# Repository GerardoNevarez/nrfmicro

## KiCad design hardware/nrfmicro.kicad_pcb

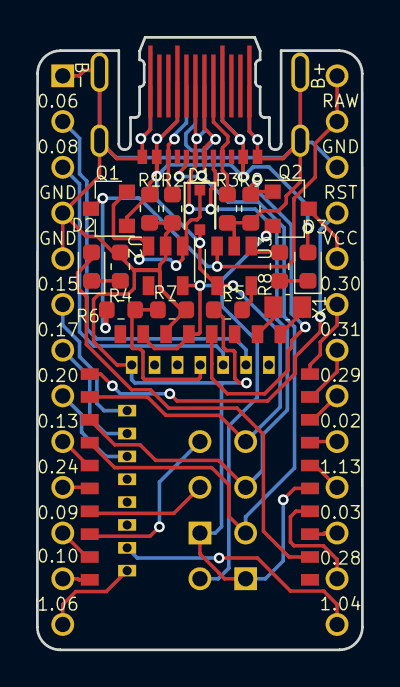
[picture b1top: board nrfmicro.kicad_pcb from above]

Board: 2 copper layers, 18.1 x 34.0 mm, 24 parts (0 on the bottom side), 40 nets.

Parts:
D1: 1N5819; D_SOD-323F
D2: BLUE; LED_0603_1608Metric
D3: RED; LED_0603_1608Metric
J1: USB-C Conn; USB-C_C168688
J2: SWD; connector_swd
J3: Ex_Bat; connector_bat
J4: Ex_USB; connector_usb
J5: USB-C Conn; USB-C-PCB
Q1, Q2: AO3407; SOT-23
R1: 100K; R_0603_1608Metric
R2, R3: 5.1K; R_0603_1608Metric
R4, R8: 1K; R_0603_1608Metric
R5: RPROG; R_0603_1608Metric
R6: 820K; R_0603_1608Metric
R7, R9: 2M; R_0603_1608Metric
U1: E73-2G4M08S1C; E73-2G4M08S1C-52840
U2: XC6220B331MR-G; SOT-23-5
U3: TP4054; SOT-23-5
U4: ProMicro; pro_micro
X1: 32.768kHz; Crystal_SMD_MicroCrystal_CM9V-T1A-2Pin_1.6x1.0mm

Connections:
/P0.00: U1.11, X1.2
/P0.01: U1.13, X1.1
/P0.02: U1.7, U4.8
/P0.03: U1.3, U4.10
/P0.06: U1.14, U4.13
/P0.08: U1.16, U4.14
/P0.09: U1.41, U4.22
/P0.10: U1.43, U4.23
/P0.13: U1.33, U4.20
/P0.15: U1.28, U4.17
/P0.17: U1.30, U4.18
/P0.20: U1.32, U4.19
/P0.24: U1.35, U4.21
/P0.28: U1.4, U4.11
/P0.29: U1.8, U4.7
/P0.30: U1.10, U4.5
/P0.31: U1.9, U4.6
/P1.04: U1.40, U4.12
/P1.06: U1.42, U4.24
/P1.13: U1.6, U4.9
BATTERY_PIN: R6.2, R7.1, U1.18
BLUE_LED: D2.2, U1.2
CC1: J1.A5, J5.A5, R3.1
CC2: J1.B5, J5.B5, R2.1
DATA+: J1.A6, J1.B6, J4.2, J5.A6, J5.B6, U1.31
DATA-: J1.A7, J1.B7, J4.3, J5.A7, J5.B7, U1.29
EXT_VCC: Q2.3, U4.4
GND: J1.A1, J1.S1, J2.2, J3.2, J4.1, J5.A1, J5.A12, J5.B1, J5.B12, R1.2, R2.2, R3.2, R4.2, R5.2, R7.2, R9.2, U1.5, U1.21, U1.24, U2.2, U3.2, U4.2, U4.15, U4.16
unnamed: D1.1, Q1.2, U2.1, U2.3
unnamed: D2.1, R4.1
unnamed: D3.1, R8.1
unnamed: R5.1, U3.5
unnamed: R8.2, U3.1
POWER_PIN: Q2.1, R9.1, U1.17
RESET: U1.26, U4.3
SWC: J2.4, U1.39
SWD: J2.3, U1.37
VBAT: J3.1, Q1.3, R6.1, U3.3, U4.1
VBUS: D1.2, D3.2, J1.A4, J4.4, J5.A4, J5.A9, J5.B4, J5.B9, Q1.1, R1.1, U1.27, U3.4
nRF_VDD: J2.1, Q2.2, U1.19, U1.23, U2.5

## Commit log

2021-07-21 Replace Pin 12 connection from P1.11 to P1.04
2021-07-21 Update Pin12 silkscreen
2021-07-21 Update Pin12 silkscreen (back)
2021-07-21 Move P1.04 via
2021-08-17 Update gerbers zip
